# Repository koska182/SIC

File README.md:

# SIC
Soldering iron control 
ATMega8 PWM PID control for Hakko 907 soldering iron
With 16x2 LCD

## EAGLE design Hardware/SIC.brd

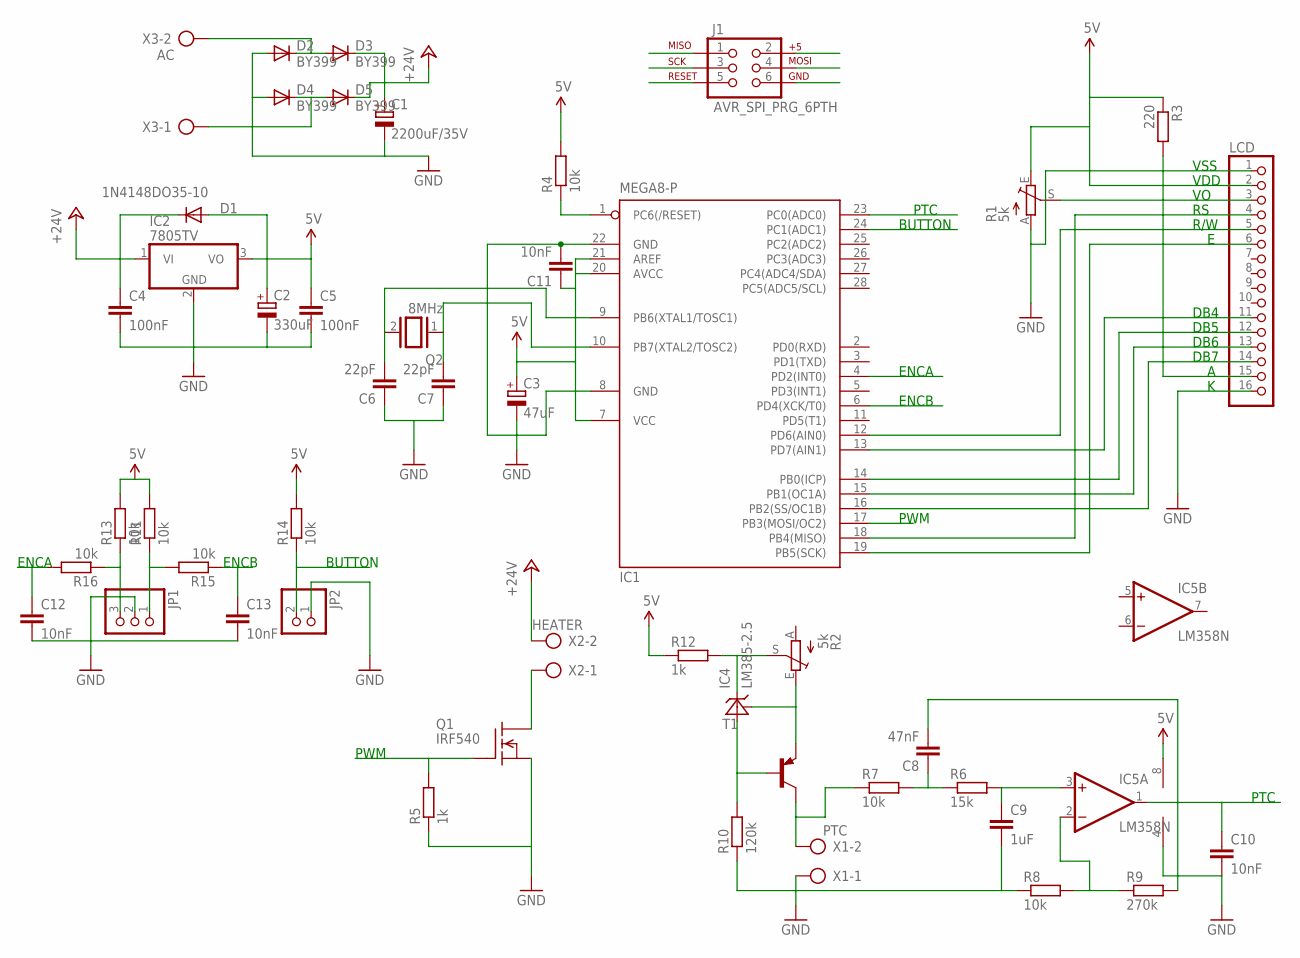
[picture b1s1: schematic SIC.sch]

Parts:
C1: 2200uF/35V; E7,5-16
C2: 330uF; E3,5-8
C3: 47uF; E2-5
C4, C5: 100nF; C050-025X075
C6, C7: 22pF; C050-024X044
C8: 47nF; C050-025X075
C9: 1uF; C050-030X075
C10, C11, C12, C13: 10nF; C050-025X075
D1: 1N4148DO35-10; DO35-10
D2, D3, D4, D5: BY399; DO201-15
IC1: MEGA8-P; DIL28-3
IC2: 7805TV; TO220V
IC4: LM385-2.5; TO92-
IC5: LM358N; DIL08
J1: AVR_SPI_PRG_6PTH; 2X3
JP1: PINHD-1X3; 1X03
JP2: PINHD-1X2; 1X02
LCD: PINHD-1X16; 1X16
Q1: IRF540; TO220
Q2: 8MHz; QS
R1, R2: 5k; LI10
R3: 220; 0207/10
R4, R7, R8, R11, R13, R14, R15, R16: 10k; 0207/10
R5, R12: 1k; 0207/10
R6: 15k; 0207/10
R9: 270k; 0207/10
R10: 120k; 0207/10
T1: BC327-16-PNP-TO92-EBC; TO92-EBC
X1: PTC; AK300/2
X2: HEATER; AK300/2
X3: AC; AK300/2

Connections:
5V: C2.+, C3.+, C5.1, C11.1, D1.A, IC1.7 (VCC), IC1.20 (AVCC), IC1.21 (AREF), IC2.3 (VO), IC5.8 (V+), J1.2, LCD.2, R1.E, R3.1, R4.2, R11.2, R12.1, R13.2, R14.2
+24V: C1.+, C4.1, D1.C, D3.C, D5.C, IC2.1 (VI), X2.2
BUTTON: IC1.24 (PC1(ADC1)), JP2.2, R14.1
ENCA: C12.1, IC1.4 (PD2(INT0)), R16.2
ENCB: C13.1, IC1.6 (PD4(XCK/T0)), R15.1
GND: C1.-, C2.-, C3.-, C4.2, C5.2, C6.1, C7.1, C9.2, C10.2, C11.2, C12.2, C13.2, D2.A, D4.A, IC1.8 (GND), IC1.22 (GND), IC2.2 (GND), IC5.4 (V-), J1.6, JP1.2, JP2.1, LCD.1, LCD.16, Q1.3 (S), R1.A, R5.1, R8.1, R10.1, X1.1
MISO: IC1.18 (PB4(MISO)), J1.1, LCD.4
MOSI_PWM: IC1.17 (PB3(MOSI/OC2)), J1.4, Q1.1 (G), R5.2
unnamed: IC1.13 (PD7(AIN1)), LCD.11
unnamed: IC1.14 (PB0(ICP)), LCD.12
unnamed: IC1.15 (PB1(OC1A)), LCD.13
unnamed: IC1.16 (PB2(SS/OC1B)), LCD.14
unnamed: LCD.15, R3.2
unnamed: C8.1, R6.1, R7.2
unnamed: C9.1, IC5.3 (+IN), R6.2
unnamed: Q1.2 (D), X2.1
unnamed: LCD.3, R1.S
unnamed: IC5.2 (-IN), R8.2, R9.1
unnamed: JP1.3, R13.1, R16.1
unnamed: D4.C, D5.A, X3.1
unnamed: D2.C, D3.A, X3.2
unnamed: R7.1, T1.C, X1.2
unnamed: IC4.3 (FB), R2.E, T1.E
unnamed: JP1.1, R11.1, R15.2
unnamed: C6.2, IC1.9 (PB6(XTAL1/TOSC1)), Q2.2
unnamed: C7.2, IC1.10 (PB7(XTAL2/TOSC2)), Q2.1
unnamed: IC1.12 (PD6(AIN0)), LCD.5
unnamed: IC4.1 (A), R10.2, T1.B
unnamed: IC4.2 (C), R2.S, R12.2
PTC: C8.2, C10.1, IC1.23 (PC0(ADC0)), IC5.1 (OUT), R9.2
RESET: IC1.1 (PC6(/RESET)), J1.5, R4.1
SCK: IC1.19 (PB5(SCK)), J1.3, LCD.6

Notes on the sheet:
PWM
PTC
BUTTON
ENCA
ENCB
DB7
DB6
DB5
DB4
R/W
VDD
VSS

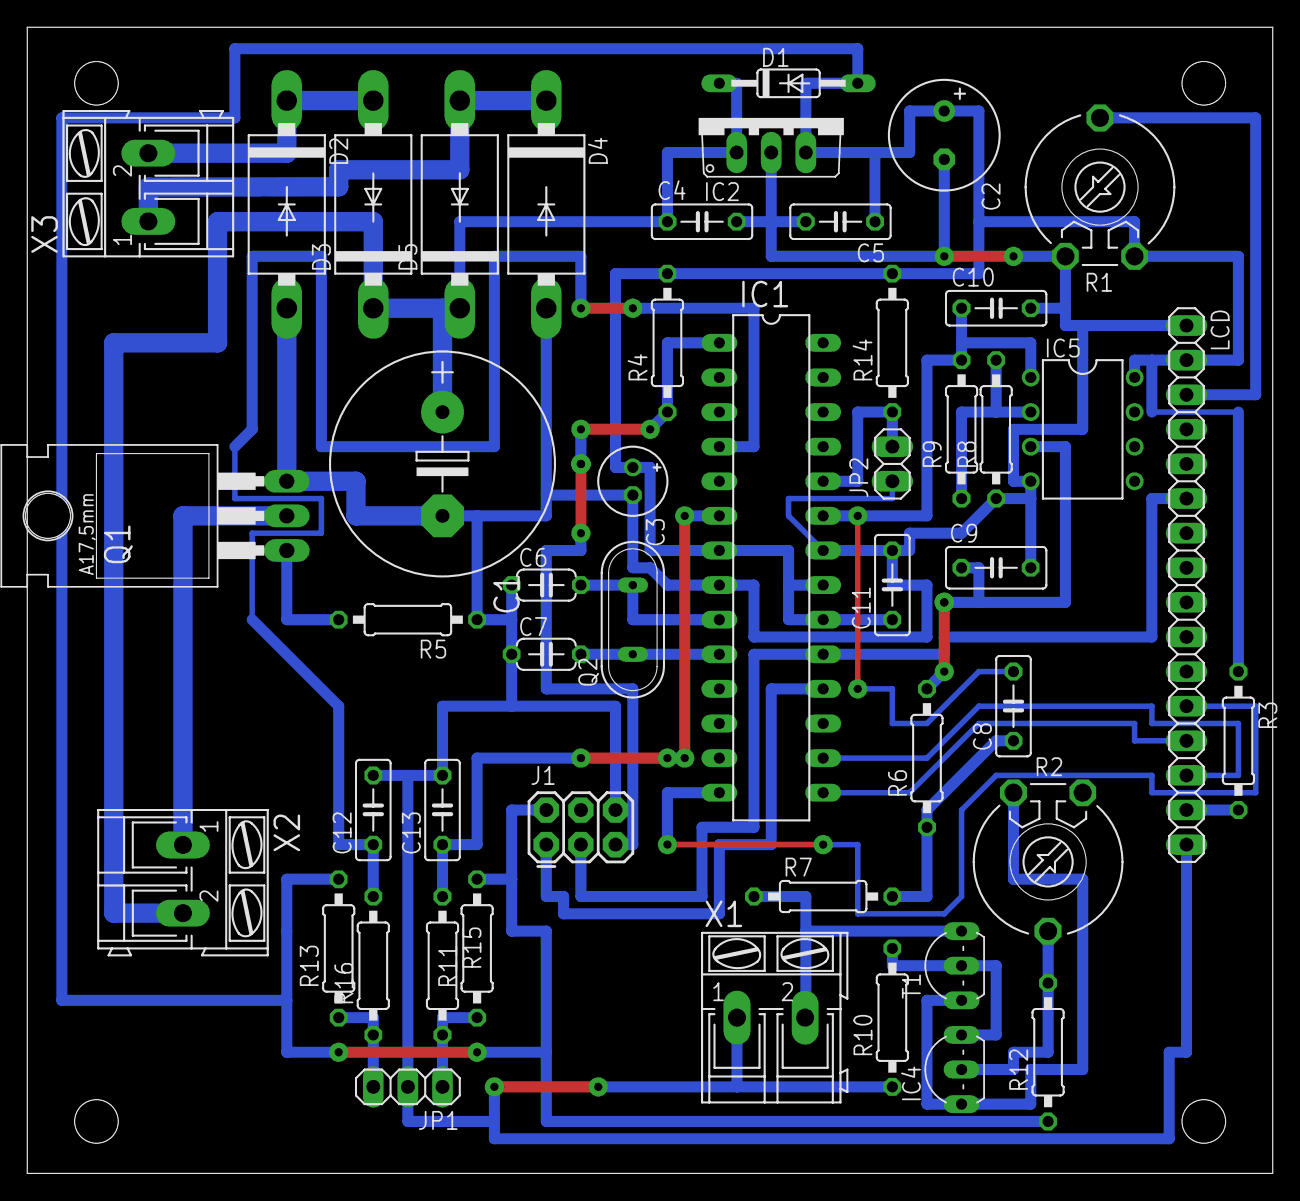
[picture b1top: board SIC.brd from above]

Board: 2 copper layers, 91.4 x 84.1 mm, 48 parts (0 on the bottom side), 32 nets.

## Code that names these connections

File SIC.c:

/*
 * SIC.c
 *
 * Created: 2.6.2015. 17:29:51
 *  Author: Aleksandar Kosanovic
 */ 

#include <avr/io.h>
/*http://homepage.hispeed.ch/peterfleury/lcdlibrary.zip*/
#define F_CPU 8000000 
#include <avr/interrupt.h>
#include <util/delay.h>
#include "lcd.h"
/*
 16x2 LCD display.  The LiquidCrystal library works with all LCD displays that are compatible with the 
 Hitachi HD44780 driver.
 
 read a rotary encoder with interrupts
 Encoder hooked up with common to GROUND,
 encoder0PinA to pin PD2, encoder0PinB to pin PD4
 it doesn't matter which encoder pin you use for A or B  

  The circuit:
 * LCD RS pin to PB4
 * LCD Enable pin to PB5
 * LCD R/W pin to PD6
 * LCD D4 pin to PD7
 * LCD D5 pin to PB0
 * LCD D6 pin to PB1
 * LCD D7 pin to PB2
 * 10K trimmer:
 * ends to +5V and ground
 * wiper to LCD VO pin (pin 3)
 
ADC input on PC0 
Button input on PC1
PWM output on PB3 (OCR2, compare output from Timer2)
 
 */

#define Kp 8		//factor in p part of controller
#define Ki 0.1		//factor in i part of controller
#define Kd 6		//factor in d part of controller
volatile uint16_t encPos = 320;
volatile uint16_t update_lcd = 1;
volatile uint8_t button_down;
static inline void debounce(void);

volatile uint16_t iState =0;
volatile uint16_t dState =0;

uint16_t UpdatePID(int16_t error, uint16_t position)
{
	int16_t pTerm, dTerm, iTerm; 
	int16_t result;

	pTerm = Kp * error;   // calculate the proportional term

	// calculate the integral state with appropriate limiting
	iState += error;
	if (iState > 255) iState = 255;
	else if (iState < 0) iState = 0;

	iTerm = Ki * iState;  // calculate the integral term

	dTerm = Kd * (dState - position);
	dState = position;
	
	result =pTerm + dTerm + iTerm;
	if (result > 255){
		result = 255;
	}
	else if (result<0){
		result = 0;
	}

	return result;
}

int main(void)
{
  float temperature;
  uint8_t heater_state=0; 
  DDRC &= ~(1<<PC1);   //PC1 set to input (button)
  // Routine to setup ADC
  uint16_t adc_value;
  DDRC &= ~(1<<PC0);	//PC0 set to input
  ADMUX = (1<<REFS0);	// ADC input channel set to PC0, Vref =VAcc
  ADCSRA = (1<<ADEN) | (1<<ADPS2) | (1<<ADPS0);
  // ADEN: Set to turn on ADC , by default it is turned off 
  //ADPS2: ADPS2 and ADPS0 set to make division factor 32 
  
  
  // Routine to setup INT0
  // Assure that pin PD2 (INT0) and PD4 are inputs
  DDRD &= ~(1<<PD4);
  DDRD &= ~(1<<PD2);
  MCUCR |= (1 << ISC01);    // set INT0 to trigger on ANY logic change
  GICR |= (1 << INT0);      // Turns on INT0
  sei();                    // turn on interrupts

  // Routine to setup PWM
  DDRB |= (1 << DDB3);        // PB3 is now an output
  OCR2 = 0;                 // set PWM for 0% duty cycle
  TCCR2 |= (1 << COM21);      // set none-inverting mode
  TCCR2 |= (1 << WGM21) | (1 << WGM20);   // set fast PWM Mode
  TCCR2 |= (1 << CS22)|(0 << CS21)|(1 << CS20);       // set prescaler to 128 and starts PWM 8/(128*256)=244 Hz
   
  lcd_init(LCD_DISP_ON); /* initialize lcd, display on, cursor on
                                  for more options for
                                  lcd_init(), view lcd.h file*/
  
  /*create custom char*/
  uint8_t stupanj[8]={
		 0b00110,
		 0b01001,
		 0b01001,
		 0b00110,
		 0b00000,
		 0b00000,
		 0b00000,
		 0b00000
  };
  	lcd_command(0x40);
  	for (uint8_t i= 0; i<8;i++){
	  	lcd_data(stupanj[i]);
  	}
  	_delay_ms(10);
  
  
  char tempbuff[10];
  lcd_clrscr();             /* clear screen of lcd */
  lcd_home();               /* bring cursor to 0,0 */
  lcd_puts("Hello");        
  lcd_gotoxy(0,1);          /* go to 2nd row 1st col */
  lcd_puts("SIC");  
  _delay_ms(1000);            /* wait 1 s */
  lcd_home();
  lcd_puts("Set Temp: "); //10 znakova
  //lcd_puts(" ");
  itoa(encPos, tempbuff,10);
  lcd_puts(tempbuff);
  lcd_puts(" ");
  lcd_data(0); //°
  lcd_puts("C");
  lcd_gotoxy(0,1);
  lcd_puts("Temp: "); //6 znakova
  lcd_gotoxy(9,1);
  lcd_puts(" ");
  lcd_data(0); //°
  lcd_puts("C");

  while(1)                      /* run continuously */
    {
		debounce();
		if (button_down)
		{ 
			button_down = 0;
			heater_state ^= (1 << 0);
			iState = 0;
		}
		if (update_lcd){
			lcd_gotoxy(10,0);
			itoa(encPos, tempbuff,10);
			lcd_puts(tempbuff);
			update_lcd=0;
		}
      ADCSRA |= (1<<ADSC); // Start conversion
      while (ADCSRA & (1<<ADSC)); // wait for conversion to complete
      adc_value = ADCW;
	  temperature = adc_value*0.1744;
	  temperature = (temperature+2.4548)*4.2688;
	  uint16_t temp = (uint16_t) temperature;
	    
	  uint16_t res = UpdatePID(encPos - temp,temp);
	  
	  if (heater_state){
		OCR2 = res;
		lcd_gotoxy(14,1);
		lcd_puts("ON");
	  }
	  else{
		OCR2 = 0;
		lcd_gotoxy(14,1);
		lcd_puts("  ");	  
	  }
	lcd_gotoxy(6,1);
	itoa(temp, tempbuff, 10);
	lcd_puts(tempbuff);
	_delay_ms(30);
	}
    
    
}
ISR (INT0_vect)
{
  // When an interrupt occurs, we only have to check the level of
	// of pin PD4 to determine the direction
	if (PIND & _BV(PD4)){
	// Increase enc
		if (encPos<450){
			encPos++;
			update_lcd=1;
			}
	}
	else{
		if (encPos>200){
		// Decrease enc
		encPos--;
		update_lcd=1;
		}
	}
}

static inline void debounce(void)
{
	// Counter for number of equal states
	static uint8_t count = 0;
	// Keeps track of current (debounced) state
	static uint8_t button_state = 0;
	// Check if button is high or low for the moment
	uint8_t current_state = (~PINC & (1<<PC1)) != 0;
	if (current_state != button_state) {
		// Button state is about to be changed, increase counter
		count++;
		if (count >= 4) {
			// The button have not bounced for four checks, change state
			button_state = current_state;
			// If the button was pressed (not released), tell main so
			if (current_state != 0) {
				button_down = 1;
			}
			count = 0;
		}
		} else {
		// Reset counter
		count = 0;
	}
}

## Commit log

2015-01-14 SIC.ino
2015-01-25 Hardware for SIC
2015-01-25 Updated hardware files
2015-02-11 Montazna Shema
2015-06-05 Updatet sowtware and hardware
2015-06-05 Update SIC.c
    Updated software
2015-06-05 Updated schematic
